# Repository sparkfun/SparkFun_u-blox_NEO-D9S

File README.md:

SparkFun GNSS Correction Data Receiver - NEO-D9S (Qwiic)
========================================

[*SparkFun GNSS Correction Data Receiver - NEO-D9S (Qwiic) (GPS-19390)*](https://www.sparkfun.com/products/19390)

The SparkFun NEO-D9S GNSS Correction Data Receiver is a satellite data receiver for L-Band correction broadcast. It can be configured for use with a variety of correction services including u-blox's PointPerfect satellite GNSS augmentation service, which provides homogenous coverage in the contiguous USA. With a clear view of the sky, especially a clear view to the South, it decodes the satellite transmission and outputs a correction stream, enabling a multi-band high-precision GNSS receiver (such as the u-blox ZED-F9P) to reach accuracies down to centimeter-level positioning without needing a separate RTK or NTRIP correction!

The board is equipped with a USB-C connector so you can hook the board to your laptop and configure the device using u-blox u-center if you want to. We've also equipped the breakout board with two Qwiic connectors, so you can connect it quickly and easily to your favorite development board and control it using our sophisticated u-blox GNSS Arduino Library. An SMA connector is included for a secure connection to an L-Band antenna. Power, I<sup>2</sup>C, UART1, UART2, and SPI are broken out to 0.1" spaced PTH pins. By connecting the NEO-D9S breakout to one of the ZED-F9P's communication ports, you will be able to know where your (or any object's) X, Y, and Z location is to better than an inch, without needing a separate correction source!

Repository Contents
-------------------
* **/Documents** - Data sheets, additional product information
* **/Hardware** - Eagle design files (.brd, .sch)

Documentation
--------------
* **[Library](https://github.com/sparkfun/SparkFun_u-blox_GNSS_Arduino_Library)** - Arduino library for the NEO-D9S.
  * **[NEO-D9S Code Example](https://github.com/sparkfun/SparkFun_u-blox_GNSS_Arduino_Library/blob/main/examples/Example30_NEO-D9S/Example30_NEO-D9S.ino)**
  * **[NEO-D9S + ZED-F9P Code Example](https://github.com/sparkfun/SparkFun_u-blox_GNSS_Arduino_Library/tree/main/examples/ZED-F9P/Example19_LBand_Corrections_with_NEO-D9S)**
* **[Hookup Guide](https://learn.sparkfun.com/tutorials/2352)** - Basic hookup guide for the NEO-D9S breakout board.

Product Versions
----------------
* [GPS-19390](https://www.sparkfun.com/products/19390) - Initial release

Version History
---------------
* v1.0 - Initial release

License Information
-------------------

This product is _**open source**_! 

Please review the LICENSE.md file for license information. 

If you have any questions or concerns on licensing, please contact technical support on our [SparkFun forums](https://forum.sparkfun.com/viewforum.php?f=152).

Distributed as-is; no warranty is given.

- Your friends at SparkFun.

_<COLLABORATION CREDIT>_

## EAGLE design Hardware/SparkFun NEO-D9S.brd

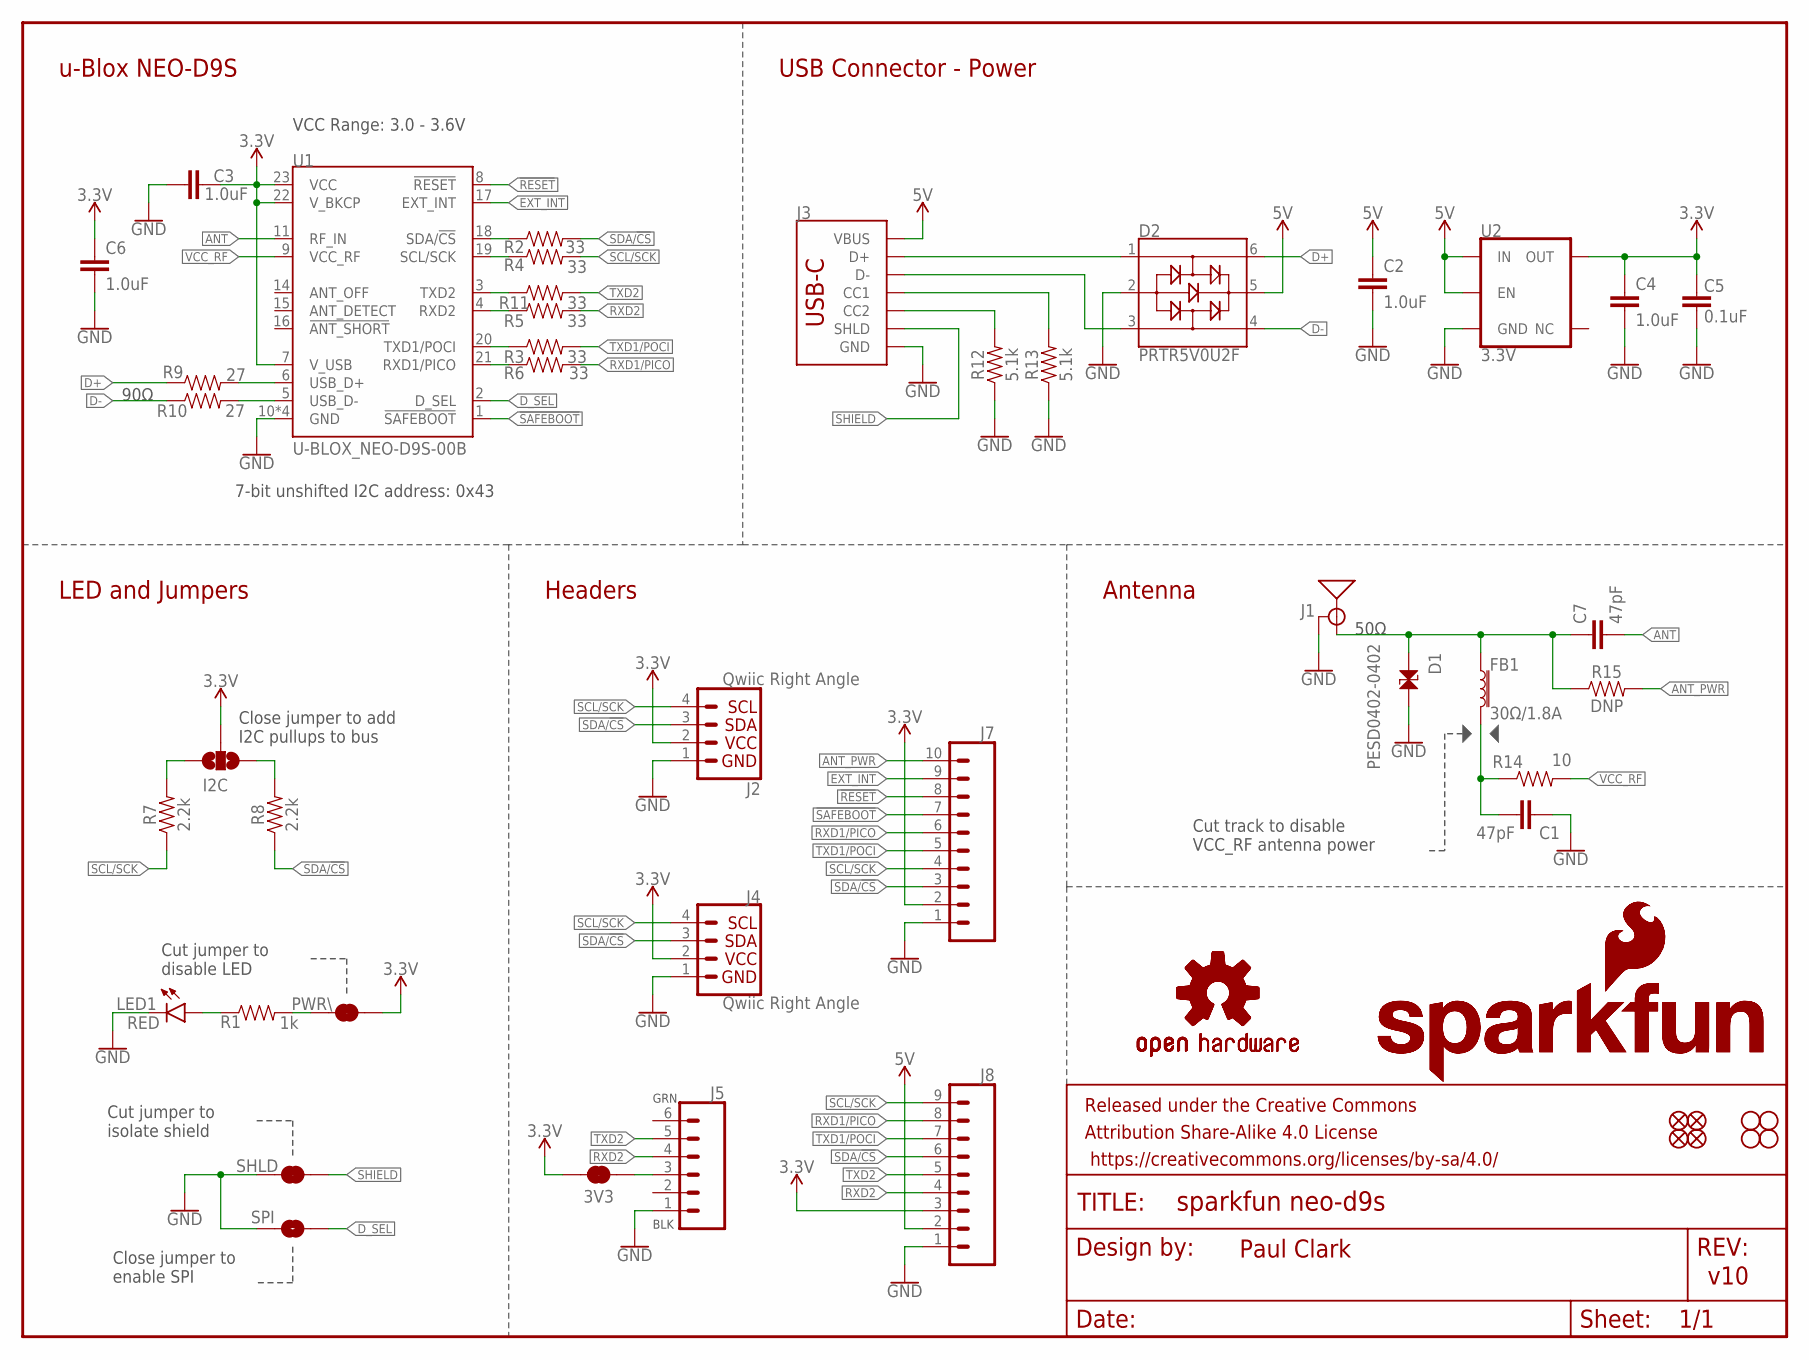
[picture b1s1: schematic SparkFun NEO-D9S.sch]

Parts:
3V3: JUMPER-SMT_2_NC_TRACE_SILK; SMT-JUMPER_2_NC_TRACE_SILK
C1, C7: 47pF; 0603
C2, C3, C4, C6: 1.0uF; 0603
C5: 0.1uF; 0603
D1: PESD0402-0402; 0402
D2: PRTR5V0U2F; SOT886
FB1: 30Ω/1.8A; 0603
FRAME1: FRAME-LETTER; CREATIVE_COMMONS
I2C: JUMPER-SMT_3_NO_SILK; SMT-JUMPER_3_NO_SILK
J1: ANTENNA-SMA-GROUNDEDEDGE_SMA; SMA-EDGE
J2, J4: Qwiic Right Angle; JST04_1MM_RA
J3: USB_C_2-LAYER_PADS; USB-C-16P-2LAYER-PADS
J5: CONN_06NO_SILK_FEMALE_PTH; 1X06_NO_SILK
J7: CONN_10NO_SILK_PTH_FEMALE; 1X10_NO_SILK
J8: CONN_09NO_SILK; 1X09_NO_SILK
JP21, JP61, JP71, JP81: FIDUCIALUFIDUCIAL; MICRO-FIDUCIAL
JP31, JP41, JP91, JP101: STAND-OFF
LED1: RED; LED-0603
LOGO1, LOGO4: OSHW-LOGOS; OSHW-LOGO-S
LOGO2, LOGO3: SFE_LOGO_NAME_FLAME.1_INCH; SFE_LOGO_NAME_FLAME_.1
PWR\: JUMPER-SMT_2_NC_TRACE_SILK; SMT-JUMPER_2_NC_TRACE_SILK
R1: 1k; 0603
R2, R3, R4, R5, R6, R11: 33; 0603
R7, R8: 2.2k; 0603
R9, R10: 27; 0603
R12, R13: 5.1k; 0603
R14: 10; 0603
R15: DNP; 0603_NO_CREAM
SHLD: JUMPER-SMT_2_NC_TRACE_SILK; SMT-JUMPER_2_NC_TRACE_SILK
SPI: JUMPER-SMT_2_NO_SILK; SMT-JUMPER_2_NO_SILK
U1: U-BLOX_NEO-D9S-00B; NEO-M9N/M8T/M8U/D9S
U2: 3.3V; SOT23-5

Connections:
3.3V: 3V3.2, C3.1, C4.1, C5.2, C6.1, I2C.2, J2.2, J4.2, J7.2, J8.3, PWR\.2, U1.7 (V_USB), U1.22 (V_BKCP), U1.23 (VCC), U2.5 (OUT)
5V: C2.1, D2.5, J3.VBUS1 (VBUS), J3.VBUS2 (VBUS), J8.2, U2.1 (IN), U2.3 (EN)
!RESET!: J7.8, U1.8 (!RESET!)
!SAFEBOOT!: J7.7, U1.1 (!SAFEBOOT!)
ANT: C7.2, U1.11 (RF_IN)
ANT_PWR: J7.10, R15.2
ANT_VCC: C1.1, FB1.2, R14.1
D+: D2.6, R9.1
D-: D2.4, R10.1
D_SEL: SPI.2, U1.2 (D_SEL)
EXT_INT: J7.9, U1.17 (EXT_INT)
GND: C1.2, C2.2, C3.2, C4.2, C5.1, C6.2, D1.2, D2.2, J1.GND@0 (GND), J1.GND@1 (GND), J1.GND@2 (GND), J1.GND@3 (GND), J2.1, J3.GND, J3.GND2 (GND), J4.1, J5.1, J7.1, J8.1, LED1.C, R12.1, R13.1, SHLD.1, SPI.1, U1.10 (GND), U1.12 (GND), U1.13 (GND), U1.24 (GND), U2.2 (GND)
unnamed: PWR\.1, R1.2
unnamed: R3.1, U1.20 (TXD1/POCI)
unnamed: R2.1, U1.18 (SDA/!CS!)
unnamed: R4.1, U1.19 (SCL/SCK)
unnamed: I2C.1, R8.2
unnamed: R6.1, U1.21 (RXD1/PICO)
unnamed: J3.B5 (CC2), R12.2
unnamed: I2C.3, R7.2
unnamed: J3.A5 (CC1), R13.2
unnamed: LED1.A, R1.1
unnamed: R9.2, U1.6 (USB_D+)
unnamed: R10.2, U1.5 (USB_D-)
unnamed: 3V3.1, J5.3
unnamed: R11.1, U1.3 (TXD2)
unnamed: R5.1, U1.4 (RXD2)
RXD1/PICO: J7.6, J8.8, R6.2
RXD2: J5.4, J8.4, R5.2
SCL/SCK: J2.4, J4.4, J7.4, J8.9, R4.2, R7.1
SDA/!CS!: J2.3, J4.3, J7.3, J8.6, R2.2, R8.1
SHIELD: J3.SHLD1 (SHLD), J3.SHLD2 (SHLD), J3.SHLD3 (SHLD), J3.SHLD4 (SHLD), SHLD.2
SMA: C7.1, D1.1, FB1.1, J1.SIG (SIGNAL), R15.1
TXD1/POCI: J7.5, J8.7, R3.2
TXD2: J5.5, J8.5, R11.2
USB_D+: D2.1, J3.A6 (D+), J3.B6 (D+)
USB_D-: D2.3, J3.A7 (D-), J3.B7 (D-)
VCC_RF: R14.2, U1.9 (VCC_RF)

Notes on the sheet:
v10
7-bit unshifted I2C address: 0x43
Close jumper to add I2C pullups to bus
Cut jumper to disable LED
Close jumper to enable SPI
Paul Clark
Headers
LED and Jumpers
u-Blox NEO-D9S
Antenna
USB Connector - Power
VCC Range: 3.0 - 3.6V
BLK
GRN
Cut jumper to isolate shield
50Ω
Cut track to disable VCC_RF antenna power
90Ω

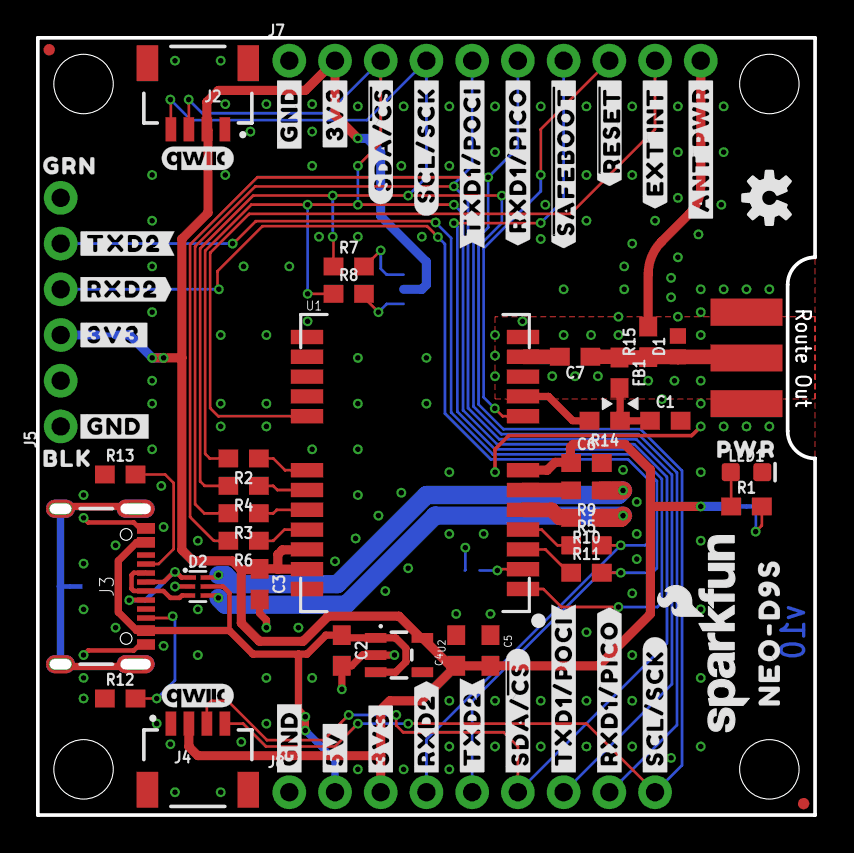
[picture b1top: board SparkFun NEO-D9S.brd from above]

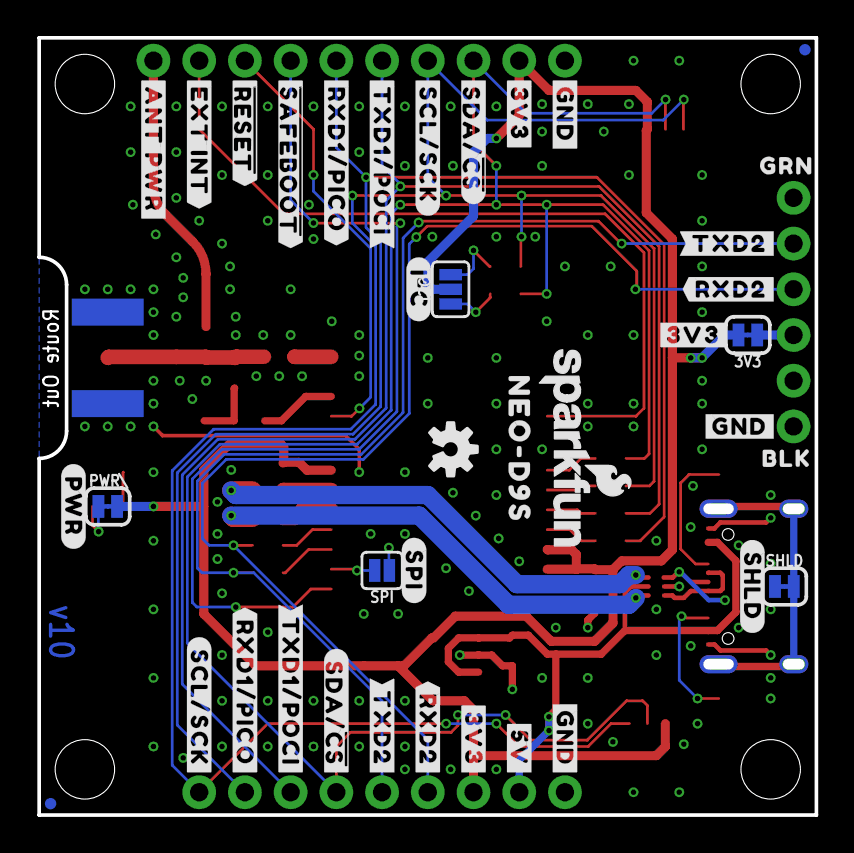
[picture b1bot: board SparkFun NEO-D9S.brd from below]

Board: 2 copper layers, 42.9 x 42.8 mm, 112 parts (39 on the bottom side), 38 nets.

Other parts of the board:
U$1, U$2, U$3: #GND#0
U$4, U$5, U$6: #GND#1
U$7, U$8: #TXD2#0
U$9, U$10: #TXD2#3
U$11, U$12: #RXD2#0
U$13, U$15: #RXD2#3
U$14, U$38: QWIIC_4MM
U$16, U$17: BLK0
U$18, U$19: GRN0
U$20: #5V#0
U$21: #5V#6
U$22, U$23, U$56, U$57: #3V3#0
U$24, U$25: #3V3#4
U$26, U$27: #SDA##CS##0
U$28, U$29: #SDA##CS##1
U$30, U$31: #TXD1#POCI#0
U$32, U$33: #TXD1#POCI#2
U$34, U$35: #RXD1#PICO#0
U$36, U$37: #RXD1#PICO#2
U$39, U$40: #SCL#SCK#0
U$41, U$42: #SCL#SCK#1
U$43: ##SAFEBOOT##0
U$44: ##SAFEBOOT##1
U$45: ##RESET##0
U$46: ##RESET##1
U$47: #EXT_INT#0
U$48: #EXT_INT#1
U$49: PWR0
U$50: #PWR#0
U$51: #SPI#0
U$52: #I�C#0
U$53: #SHLD#0
U$54, U$55: NEO#D9S0
U$58: #ANT_PWR#0
U$59: #ANT_PWR#1

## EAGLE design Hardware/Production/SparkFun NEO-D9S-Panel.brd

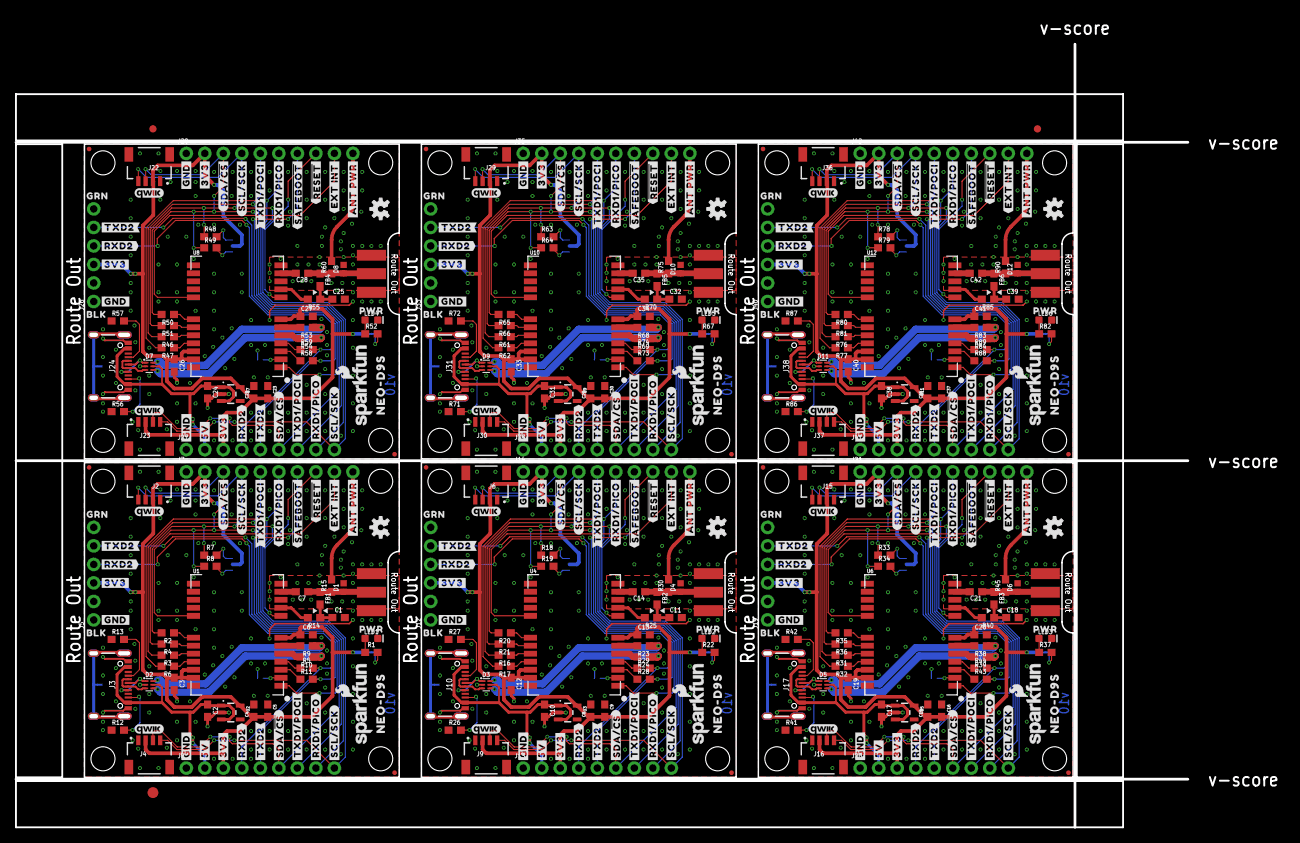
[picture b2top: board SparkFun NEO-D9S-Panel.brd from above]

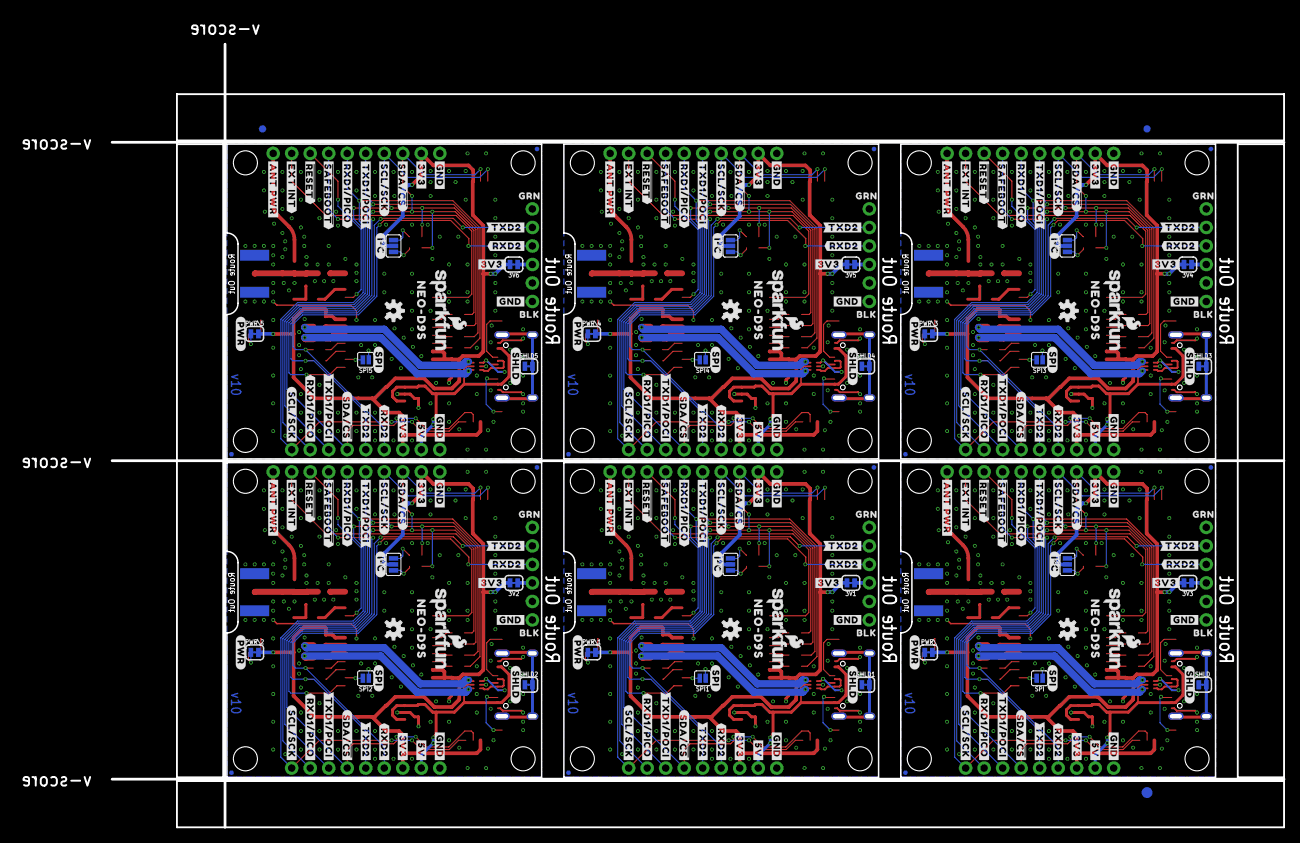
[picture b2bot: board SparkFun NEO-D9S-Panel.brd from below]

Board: 2 copper layers, 173.8 x 111.1 mm, 672 parts (237 on the bottom side), 228 nets.

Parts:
3V1, 3V2, 3V3, 3V4, 3V5, 3V6: JUMPER-SMT_2_NC_TRACE_SILK; SMT-JUMPER_2_NC_TRACE_SILK
C1, C7, C11, C14, C18, C21, C25, C28, C32, C35, C39, C42: 47pF; 0603
C2, C3, C4, C6, C8, C10, C12, C13, C15, C17, C19, C20, C22, C24, C26, C27, C29, C31, C33, C34, C36, C38, C40, C41: 1.0uF; 0603
C5, C9, C16, C23, C30, C37: 0.1uF; 0603
D1, D4, D6, D8, D10, D12: PESD0402-0402; 0402
D2, D3, D5, D7, D9, D11: PRTR5V0U2F; SOT886
E$1, E$2, E$3, E$4: FIDUCIAL-1X2
E$5, E$6: FIDUCIAL-1.5X3
FB1, FB2, FB3, FB4, FB5, FB6: 30Ω/1.8A; 0603
I2C, I2C1, I2C2, I2C3, I2C4, I2C5: JUMPER-SMT_3_NO_SILK; SMT-JUMPER_3_NO_SILK
J1, J11, J18, J25, J32, J39: ANTENNA-SMA-GROUNDEDEDGE_SMA; SMA-EDGE
J2, J4, J6, J9, J15, J16, J22, J23, J29, J30, J36, J37: Qwiic Right Angle; JST04_1MM_RA
J3, J10, J17, J24, J31, J38: USB-C-16P-2LAYER-PADS
J5, J12, J19, J26, J33, J40: 1X06_NO_SILK
J7, J14, J21, J28, J35, J42: 1X10_NO_SILK
J8, J13, J20, J27, J34, J41: 1X09_NO_SILK
JP1, JP2, JP7, JP8, JP9, JP10, JP15, JP16, JP17, JP18, JP24, JP25, JP26, JP27, JP31, JP33, JP34, JP35, JP36, JP41, JP42, JP43, JP91, JP101: STAND-OFF
JP3, JP4, JP5, JP6, JP11, JP12, JP13, JP14, JP19, JP20, JP21, JP22, JP23, JP28, JP29, JP30, JP32, JP37, JP38, JP39, JP40, JP61, JP71, JP81: FIDUCIALUFIDUCIAL; MICRO-FIDUCIAL
LED1, LED2, LED3, LED4, LED5, LED6: RED; LED-0603
LOGO1, LOGO4, LOGO5, LOGO8, LOGO9, LOGO12, LOGO13, LOGO16, LOGO17, LOGO20, LOGO21, LOGO24: OSHW-LOGOS; OSHW-LOGO-S
LOGO2, LOGO3, LOGO6, LOGO7, LOGO10, LOGO11, LOGO14, LOGO15, LOGO18, LOGO19, LOGO22, LOGO23: SFE_LOGO_NAME_FLAME.1_INCH; SFE_LOGO_NAME_FLAME_.1
PWR\, PWR\1, PWR\2, PWR\3, PWR\4, PWR\5: JUMPER-SMT_2_NC_TRACE_SILK; SMT-JUMPER_2_NC_TRACE_SILK
R1, R22, R37, R52, R67, R82: 1k; 0603
R2, R3, R4, R5, R6, R11, R16, R17, R20, R21, R28, R29, R31, R32, R35, R36, R43, R44, R46, R47, R50, R51, R58, R59, R61, R62, R65, R66, R73, R74, R76, R77, R80, R81, R88, R89: 33; 0603
R7, R8, R18, R19, R33, R34, R48, R49, R63, R64, R78, R79: 2.2k; 0603
R9, R10, R23, R24, R38, R39, R53, R54, R68, R69, R83, R84: 27; 0603
R12, R13, R26, R27, R41, R42, R56, R57, R71, R72, R86, R87: 5.1k; 0603
R14, R25, R40, R55, R70, R85: 10; 0603
R15, R30, R45, R60, R75, R90: DNP; 0603_NO_CREAM
SHLD, SHLD1, SHLD2, SHLD3, SHLD4, SHLD5: JUMPER-SMT_2_NC_TRACE_SILK; SMT-JUMPER_2_NC_TRACE_SILK
SPI, SPI1, SPI2, SPI3, SPI4, SPI5: JUMPER-SMT_2_NO_SILK; SMT-JUMPER_2_NO_SILK
U1, U4, U6, U8, U10, U12: U-BLOX_NEO-D9S-00B; NEO-M9N/M8T/M8U/D9S
U2, U3, U5, U7, U9, U11: 3.3V; SOT23-5
U$1, U$2, U$3, U$61, U$62, U$63, U$120, U$121, U$122, U$179, U$180, U$181, U$238, U$239, U$240, U$297, U$298, U$299: #GND#0
U$4, U$5, U$6, U$64, U$65, U$66, U$123, U$124, U$125, U$182, U$183, U$184, U$241, U$242, U$243, U$300, U$301, U$302: #GND#1
U$7, U$8, U$67, U$68, U$126, U$127, U$185, U$186, U$244, U$245, U$303, U$304: #TXD2#0
U$9, U$10, U$69, U$70, U$128, U$129, U$187, U$188, U$246, U$247, U$305, U$306: #TXD2#3
U$11, U$12, U$71, U$72, U$130, U$131, U$189, U$190, U$248, U$249, U$307, U$308: #RXD2#0
U$13, U$15, U$73, U$74, U$132, U$133, U$191, U$192, U$250, U$251, U$309, U$310: #RXD2#3
U$14, U$38, U$60, U$114, U$119, U$173, U$178, U$232, U$237, U$291, U$296, U$350: QWIIC_4MM
U$16, U$17, U$75, U$76, U$134, U$135, U$193, U$194, U$252, U$253, U$311, U$312: BLK0
U$18, U$19, U$77, U$78, U$136, U$137, U$195, U$196, U$254, U$255, U$313, U$314: GRN0
U$20, U$79, U$138, U$197, U$256, U$315: #5V#0
U$21, U$80, U$139, U$198, U$257, U$316: #5V#6
U$22, U$23, U$56, U$57, U$81, U$82, U$115, U$116, U$140, U$141, U$174, U$175, U$199, U$200, U$233, U$234, U$258, U$259, U$292, U$293, U$317, U$318, U$351, U$352: #3V3#0
U$24, U$25, U$83, U$84, U$142, U$143, U$201, U$202, U$260, U$261, U$319, U$320: #3V3#4
U$26, U$27, U$85, U$86, U$144, U$145, U$203, U$204, U$262, U$263, U$321, U$322: #SDA##CS##0
U$28, U$29, U$87, U$88, U$146, U$147, U$205, U$206, U$264, U$265, U$323, U$324: #SDA##CS##1
U$30, U$31, U$106, U$107, U$165, U$166, U$224, U$225, U$283, U$284, U$342, U$343: #TXD1#POCI#0
U$32, U$33, U$108, U$109, U$167, U$168, U$226, U$227, U$285, U$286, U$344, U$345: #TXD1#POCI#2
U$34, U$35, U$110, U$111, U$169, U$170, U$228, U$229, U$287, U$288, U$346, U$347: #RXD1#PICO#0
U$36, U$37, U$112, U$113, U$171, U$172, U$230, U$231, U$289, U$290, U$348, U$349: #RXD1#PICO#2
U$39, U$40, U$89, U$90, U$148, U$149, U$207, U$208, U$266, U$267, U$325, U$326: #SCL#SCK#0
U$41, U$42, U$91, U$92, U$150, U$151, U$209, U$210, U$268, U$269, U$327, U$328: #SCL#SCK#1
U$43, U$93, U$152, U$211, U$270, U$329: ##SAFEBOOT##0
U$44, U$94, U$153, U$212, U$271, U$330: ##SAFEBOOT##1
U$45, U$95, U$154, U$213, U$272, U$331: ##RESET##0
U$46, U$96, U$155, U$214, U$273, U$332: ##RESET##1
U$47, U$97, U$156, U$215, U$274, U$333: #EXT_INT#0
U$48, U$98, U$157, U$216, U$275, U$334: #EXT_INT#1
U$49, U$99, U$158, U$217, U$276, U$335: PWR0
U$50, U$100, U$159, U$218, U$277, U$336: #PWR#0
U$51, U$101, U$160, U$219, U$278, U$337: #SPI#0
U$52, U$102, U$161, U$220, U$279, U$338: #I�C#0
U$53, U$103, U$162, U$221, U$280, U$339: #SHLD#0
U$54, U$55, U$104, U$105, U$163, U$164, U$222, U$223, U$281, U$282, U$340, U$341: NEO#D9S0
U$58, U$117, U$176, U$235, U$294, U$353: #ANT_PWR#0
U$59, U$118, U$177, U$236, U$295, U$354: #ANT_PWR#1

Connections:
3.3V: 3V3.2, C3.1, C4.1, C5.2, C6.1, I2C.2, J2.2, J4.2, J7.2, J8.3, PWR\.2, U1.7, U1.22, U1.23, U2.5
3.3V1: 3V1.2, C8.1, C9.2, C12.1, C13.1, I2C1.2, J6.2, J9.2, J13.3, J14.2, PWR\1.2, U3.5, U4.7, U4.22, U4.23
3.3V2: 3V2.2, C15.1, C16.2, C19.1, C20.1, I2C2.2, J15.2, J16.2, J20.3, J21.2, PWR\2.2, U5.5, U6.7, U6.22, U6.23
3.3V3: 3V4.2, C22.1, C23.2, C26.1, C27.1, I2C3.2, J22.2, J23.2, J27.3, J28.2, PWR\3.2, U7.5, U8.7, U8.22, U8.23
3.3V4: 3V5.2, C29.1, C30.2, C33.1, C34.1, I2C4.2, J29.2, J30.2, J34.3, J35.2, PWR\4.2, U9.5, U10.7, U10.22, U10.23
3.3V5: 3V6.2, C36.1, C37.2, C40.1, C41.1, I2C5.2, J36.2, J37.2, J41.3, J42.2, PWR\5.2, U11.5, U12.7, U12.22, U12.23
5V: C2.1, D2.5, J3.VBUS1, J3.VBUS2, J8.2, U2.1, U2.3
5V1: C10.1, D3.5, J10.VBUS1, J10.VBUS2, J13.2, U3.1, U3.3
5V2: C17.1, D5.5, J17.VBUS1, J17.VBUS2, J20.2, U5.1, U5.3
5V3: C24.1, D7.5, J24.VBUS1, J24.VBUS2, J27.2, U7.1, U7.3
5V4: C31.1, D9.5, J31.VBUS1, J31.VBUS2, J34.2, U9.1, U9.3
5V5: C38.1, D11.5, J38.VBUS1, J38.VBUS2, J41.2, U11.1, U11.3
!RESET!: J7.8, U1.8
!RESET!1: J14.8, U4.8
!RESET!2: J21.8, U6.8
!RESET!3: J28.8, U8.8
!RESET!4: J35.8, U10.8
!RESET!5: J42.8, U12.8
!SAFEBOOT!: J7.7, U1.1
!SAFEBOOT!1: J14.7, U4.1
!SAFEBOOT!2: J21.7, U6.1
!SAFEBOOT!3: J28.7, U8.1
!SAFEBOOT!4: J35.7, U10.1
!SAFEBOOT!5: J42.7, U12.1
ANT: C7.2, U1.11
ANT1: C14.2, U4.11
ANT2: C21.2, U6.11
ANT3: C28.2, U8.11
ANT4: C35.2, U10.11
ANT5: C42.2, U12.11
ANT_PWR: J7.10, R15.2
ANT_PWR1: J14.10, R30.2
ANT_PWR2: J21.10, R45.2
ANT_PWR3: J28.10, R60.2
ANT_PWR4: J35.10, R75.2
ANT_PWR5: J42.10, R90.2
ANT_VCC: C1.1, FB1.2, R14.1
ANT_VCC1: C11.1, FB2.2, R25.1
ANT_VCC2: C18.1, FB3.2, R40.1
ANT_VCC3: C25.1, FB4.2, R55.1
ANT_VCC4: C32.1, FB5.2, R70.1
ANT_VCC5: C39.1, FB6.2, R85.1
D+: D2.6, R9.1
D+1: D3.6, R23.1
D+2: D5.6, R38.1
D+3: D7.6, R53.1
D+4: D9.6, R68.1
D+5: D11.6, R83.1
D-: D2.4, R10.1
D-1: D3.4, R24.1
D-2: D5.4, R39.1
D-3: D7.4, R54.1
D-4: D9.4, R69.1
D-5: D11.4, R84.1
D_SEL: SPI.2, U1.2
D_SEL1: SPI1.2, U4.2
D_SEL2: SPI2.2, U6.2
D_SEL3: SPI3.2, U8.2
D_SEL4: SPI4.2, U10.2
D_SEL5: SPI5.2, U12.2
EXT_INT: J7.9, U1.17
EXT_INT1: J14.9, U4.17
EXT_INT2: J21.9, U6.17
EXT_INT3: J28.9, U8.17
EXT_INT4: J35.9, U10.17
EXT_INT5: J42.9, U12.17
GND: C1.2, C2.2, C3.2, C4.2, C5.1, C6.2, D1.2, D2.2, J1.GND@0, J1.GND@1, J1.GND@2, J1.GND@3, J2.1, J3.GND, J3.GND2, J4.1, J5.1, J7.1, J8.1, LED1.C, R12.1, R13.1, SHLD.1, SPI.1, U1.10, U1.12, U1.13, U1.24, U2.2
GND1: C8.2, C9.1, C10.2, C11.2, C12.2, C13.2, D3.2, D4.2, J6.1, J9.1, J10.GND, J10.GND2, J11.GND@0, J11.GND@1, J11.GND@2, J11.GND@3, J12.1, J13.1, J14.1, LED2.C, R26.1, R27.1, SHLD1.1, SPI1.1, U3.2, U4.10, U4.12, U4.13, U4.24
GND2: C15.2, C16.1, C17.2, C18.2, C19.2, C20.2, D5.2, D6.2, J15.1, J16.1, J17.GND, J17.GND2, J18.GND@0, J18.GND@1, J18.GND@2, J18.GND@3, J19.1, J20.1, J21.1, LED3.C, R41.1, R42.1, SHLD2.1, SPI2.1, U5.2, U6.10, U6.12, U6.13, U6.24
GND3: C22.2, C23.1, C24.2, C25.2, C26.2, C27.2, D7.2, D8.2, J22.1, J23.1, J24.GND, J24.GND2, J25.GND@0, J25.GND@1, J25.GND@2, J25.GND@3, J26.1, J27.1, J28.1, LED4.C, R56.1, R57.1, SHLD3.1, SPI3.1, U7.2, U8.10, U8.12, U8.13, U8.24
GND4: C29.2, C30.1, C31.2, C32.2, C33.2, C34.2, D9.2, D10.2, J29.1, J30.1, J31.GND, J31.GND2, J32.GND@0, J32.GND@1, J32.GND@2, J32.GND@3, J33.1, J34.1, J35.1, LED5.C, R71.1, R72.1, SHLD4.1, SPI4.1, U9.2, U10.10, U10.12, U10.13, U10.24
GND5: C36.2, C37.1, C38.2, C39.2, C40.2, C41.2, D11.2, D12.2, J36.1, J37.1, J38.GND, J38.GND2, J39.GND@0, J39.GND@1, J39.GND@2, J39.GND@3, J40.1, J41.1, J42.1, LED6.C, R86.1, R87.1, SHLD5.1, SPI5.1, U11.2, U12.10, U12.12, U12.13, U12.24
unnamed: PWR\.1, R1.2
unnamed: R3.1, U1.20
unnamed: R2.1, U1.18
unnamed: R4.1, U1.19
unnamed: I2C.1, R8.2
unnamed: R6.1, U1.21
unnamed: J3.B5, R12.2
unnamed: I2C.3, R7.2
unnamed: J3.A5, R13.2
unnamed: LED1.A, R1.1
unnamed: R9.2, U1.6
unnamed: R10.2, U1.5
unnamed: 3V3.1, J5.3
unnamed: R11.1, U1.3
unnamed: R5.1, U1.4
unnamed: I2C1.1, R19.2
unnamed: I2C1.3, R18.2
unnamed: LED2.A, R22.1
unnamed: R23.2, U4.6
unnamed: R24.2, U4.5
unnamed: PWR\1.1, R22.2
unnamed: J10.B5, R26.2
unnamed: J10.A5, R27.2
unnamed: R28.1, U4.3
unnamed: R29.1, U4.4
unnamed: R16.1, U4.20
unnamed: R17.1, U4.21
unnamed: R20.1, U4.18
unnamed: R21.1, U4.19
unnamed: 3V1.1, J12.3
unnamed: I2C2.1, R34.2
unnamed: I2C2.3, R33.2
unnamed: LED3.A, R37.1
unnamed: R38.2, U6.6
unnamed: R39.2, U6.5
unnamed: PWR\2.1, R37.2
unnamed: J17.B5, R41.2
unnamed: J17.A5, R42.2
unnamed: R43.1, U6.3
unnamed: R44.1, U6.4
unnamed: R31.1, U6.20
unnamed: R32.1, U6.21
unnamed: R35.1, U6.18
unnamed: R36.1, U6.19
unnamed: 3V2.1, J19.3
unnamed: I2C3.1, R49.2
unnamed: I2C3.3, R48.2
unnamed: LED4.A, R52.1
unnamed: R53.2, U8.6
unnamed: R54.2, U8.5
unnamed: PWR\3.1, R52.2
unnamed: J24.B5, R56.2
unnamed: J24.A5, R57.2
unnamed: R58.1, U8.3
unnamed: R59.1, U8.4
unnamed: R46.1, U8.20
unnamed: R47.1, U8.21
unnamed: R50.1, U8.18
unnamed: R51.1, U8.19
unnamed: 3V4.1, J26.3
unnamed: I2C4.1, R64.2
unnamed: I2C4.3, R63.2
unnamed: LED5.A, R67.1
unnamed: R68.2, U10.6
unnamed: R69.2, U10.5
unnamed: PWR\4.1, R67.2
unnamed: J31.B5, R71.2
unnamed: J31.A5, R72.2
unnamed: R73.1, U10.3
unnamed: R74.1, U10.4
unnamed: R61.1, U10.20
unnamed: R62.1, U10.21
unnamed: R65.1, U10.18
unnamed: R66.1, U10.19
unnamed: 3V5.1, J33.3
unnamed: I2C5.1, R79.2
unnamed: I2C5.3, R78.2
unnamed: LED6.A, R82.1
unnamed: R83.2, U12.6
unnamed: R84.2, U12.5
unnamed: PWR\5.1, R82.2
unnamed: J38.B5, R86.2
unnamed: J38.A5, R87.2
unnamed: R88.1, U12.3
unnamed: R89.1, U12.4
unnamed: R76.1, U12.20
unnamed: R77.1, U12.21
unnamed: R80.1, U12.18
unnamed: R81.1, U12.19
unnamed: 3V6.1, J40.3
RXD1: J12.4, J13.4, R29.2
RXD1/PICO: J7.6, J8.8, R6.2
RXD1/PICO1: J13.8, J14.6, R17.2
RXD1/PICO2: J20.8, J21.6, R32.2
RXD1/PICO3: J27.8, J28.6, R47.2
RXD1/PICO4: J34.8, J35.6, R62.2
RXD1/PICO5: J41.8, J42.6, R77.2
RXD2: J5.4, J8.4, R5.2
RXD3: J19.4, J20.4, R44.2
RXD4: J26.4, J27.4, R59.2
RXD5: J33.4, J34.4, R74.2
RXD6: J40.4, J41.4, R89.2
SCL/SCK: J2.4, J4.4, J7.4, J8.9, R4.2, R7.1
SCL/SCK1: J6.4, J9.4, J13.9, J14.4, R18.1, R21.2
SCL/SCK2: J15.4, J16.4, J20.9, J21.4, R33.1, R36.2
SCL/SCK3: J22.4, J23.4, J27.9, J28.4, R48.1, R51.2
SCL/SCK4: J29.4, J30.4, J34.9, J35.4, R63.1, R66.2
SCL/SCK5: J36.4, J37.4, J41.9, J42.4, R78.1, R81.2
SDA/!CS!: J2.3, J4.3, J7.3, J8.6, R2.2, R8.1
SDA/!CS!1: J6.3, J9.3, J13.6, J14.3, R19.1, R20.2
SDA/!CS!2: J15.3, J16.3, J20.6, J21.3, R34.1, R35.2
SDA/!CS!3: J22.3, J23.3, J27.6, J28.3, R49.1, R50.2
SDA/!CS!4: J29.3, J30.3, J34.6, J35.3, R64.1, R65.2
SDA/!CS!5: J36.3, J37.3, J41.6, J42.3, R79.1, R80.2
SHIELD: J3.SHLD1, J3.SHLD2, J3.SHLD3, J3.SHLD4, SHLD.2
SHIELD1: J10.SHLD1, J10.SHLD2, J10.SHLD3, J10.SHLD4, SHLD1.2
SHIELD2: J17.SHLD1, J17.SHLD2, J17.SHLD3, J17.SHLD4, SHLD2.2
SHIELD3: J24.SHLD1, J24.SHLD2, J24.SHLD3, J24.SHLD4, SHLD3.2
SHIELD4: J31.SHLD1, J31.SHLD2, J31.SHLD3, J31.SHLD4, SHLD4.2
SHIELD5: J38.SHLD1, J38.SHLD2, J38.SHLD3, J38.SHLD4, SHLD5.2
SMA: C7.1, D1.1, FB1.1, J1.SIG, R15.1
SMA1: C14.1, D4.1, FB2.1, J11.SIG, R30.1
SMA2: C21.1, D6.1, FB3.1, J18.SIG, R45.1
SMA3: C28.1, D8.1, FB4.1, J25.SIG, R60.1
SMA4: C35.1, D10.1, FB5.1, J32.SIG, R75.1
SMA5: C42.1, D12.1, FB6.1, J39.SIG, R90.1
TXD1: J12.5, J13.5, R28.2
TXD1/POCI: J7.5, J8.7, R3.2
TXD1/POCI1: J13.7, J14.5, R16.2
TXD1/POCI2: J20.7, J21.5, R31.2
TXD1/POCI3: J27.7, J28.5, R46.2
TXD1/POCI4: J34.7, J35.5, R61.2
TXD1/POCI5: J41.7, J42.5, R76.2
TXD2: J5.5, J8.5, R11.2
TXD3: J19.5, J20.5, R43.2
TXD4: J26.5, J27.5, R58.2
TXD5: J33.5, J34.5, R73.2
TXD6: J40.5, J41.5, R88.2
USB_D+: D2.1, J3.A6, J3.B6
USB_D+1: D3.1, J10.A6, J10.B6
USB_D+2: D5.1, J17.A6, J17.B6
USB_D+3: D7.1, J24.A6, J24.B6
USB_D+4: D9.1, J31.A6, J31.B6
USB_D+5: D11.1, J38.A6, J38.B6
USB_D-: D2.3, J3.A7, J3.B7
USB_D-1: D3.3, J10.A7, J10.B7
USB_D-2: D5.3, J17.A7, J17.B7
USB_D-3: D7.3, J24.A7, J24.B7
USB_D-4: D9.3, J31.A7, J31.B7
USB_D-5: D11.3, J38.A7, J38.B7
VCC_RF: R14.2, U1.9
VCC_RF1: R25.2, U4.9
VCC_RF2: R40.2, U6.9
VCC_RF3: R55.2, U8.9
VCC_RF4: R70.2, U10.9
VCC_RF5: R85.2, U12.9

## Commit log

2022-02-08 Routed. Add schematic
2022-02-08 Add C6
2022-02-08 Final tweaks. Ready for proto review.
2022-02-08 Add the documents
2022-02-09 Add cut marks for antenna power
2022-02-11 Post-Proto Review Changes
2022-02-16 Add PROD_ID for NEO-D9S-00B. Add Proto production files
2022-03-25 Updates for v10 PCB
2022-03-29 Updates after REDs Review
2022-04-07 Update schematic
2025-02-21 Update L-Band coverage

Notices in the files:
parts and their libraries:
SparkFun-Resistors: Licensing: Creative Commons ShareAlike 4.0 International - https://creativecommons.org/licenses/by-sa/4.0
SparkFun-Aesthetics: Released under the Creative Commons Attribution Share-Alike 4.0 License
SparkFun-Aesthetics: https://creativecommons.org/licenses/by-sa/4.0
